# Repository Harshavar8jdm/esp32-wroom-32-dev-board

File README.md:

# ESP32-WROOM-32 Custom Development Board
**Designed by HTronics (Harsha Ganesh)**

A custom, breadboard-friendly development board for the ESP32-WROOM-32 module. This board features a modern USB-C interface, reliable serial communication via the CH340C, and an automatic bootloader entry circuit for seamless flashing.

</div>

---

## 📸 Project Showcase

### 3D Renders

### PCB Layout & Schematic

---

## ✨ Key Features

* **Modern Connectivity:** USB 2.0 Type-C receptacle with 5.1kΩ pull-down resistors on the CC lines, ensuring compatibility with standard Type-A to Type-C and Type-C to Type-C cables.
* **Auto-Programming Circuit:** Built-in two-transistor (SS8050) auto-reset circuit driven by DTR/RTS lines. No need to hold the "BOOT" button to flash firmware.
* **Robust Power Delivery:** Uses the AMS1117-3.3 LDO to step down 5V VBUS to a stable 3.3V for the ESP32, paired with 100nF and 10uF decoupling capacitors. Includes a B5819W Schottky diode for back-power protection.
* **USB-to-UART:** CH340C bridge provides reliable serial communication without requiring an external crystal oscillator.
* **User I/O:** Includes standard EN (Reset) and IO0 (Boot) tactile switches, a dedicated Red power LED, and a Green user LED mapped to GPIO 2.
* **Breadboard Friendly:** 2x15 pin headers break out all essential ESP32 GPIOs, strapping pins, and power rails.

---

## 🛠️ Hardware Overview & Schematic Sections

### 1. Power Supply (`AMS1117-3.3`)
The board takes 5V input from the USB-C VBUS line. A B5819W reverse-polarity protection diode prevents current from feeding back into the host device. The AMS1117-3.3 low-dropout regulator supplies up to 1A of 3.3V power, more than sufficient for the ESP32's RF transmission peaks. 

### 2. USB-to-UART Bridge (`CH340C`)
The CH340C handles USB data enumeration. 
* **Driver Note:** If you are using Linux (e.g., Fedora, Ubuntu), the CH340 driver is already built directly into the kernel—making it truly plug-and-play without any manual DNF/APT installations. Windows and macOS users may need to install the official WCH drivers.

### 3. Auto-Reset Circuit (`SS8050 Transistors`)
The CH340C toggles the `DTR` and `RTS` pins during the firmware upload sequence. The two SS8050 NPN transistors translate these signals into the precise timing sequence required to pull `EN` (Reset) low while `IO0` is held low, putting the ESP32 into flash mode automatically.

---

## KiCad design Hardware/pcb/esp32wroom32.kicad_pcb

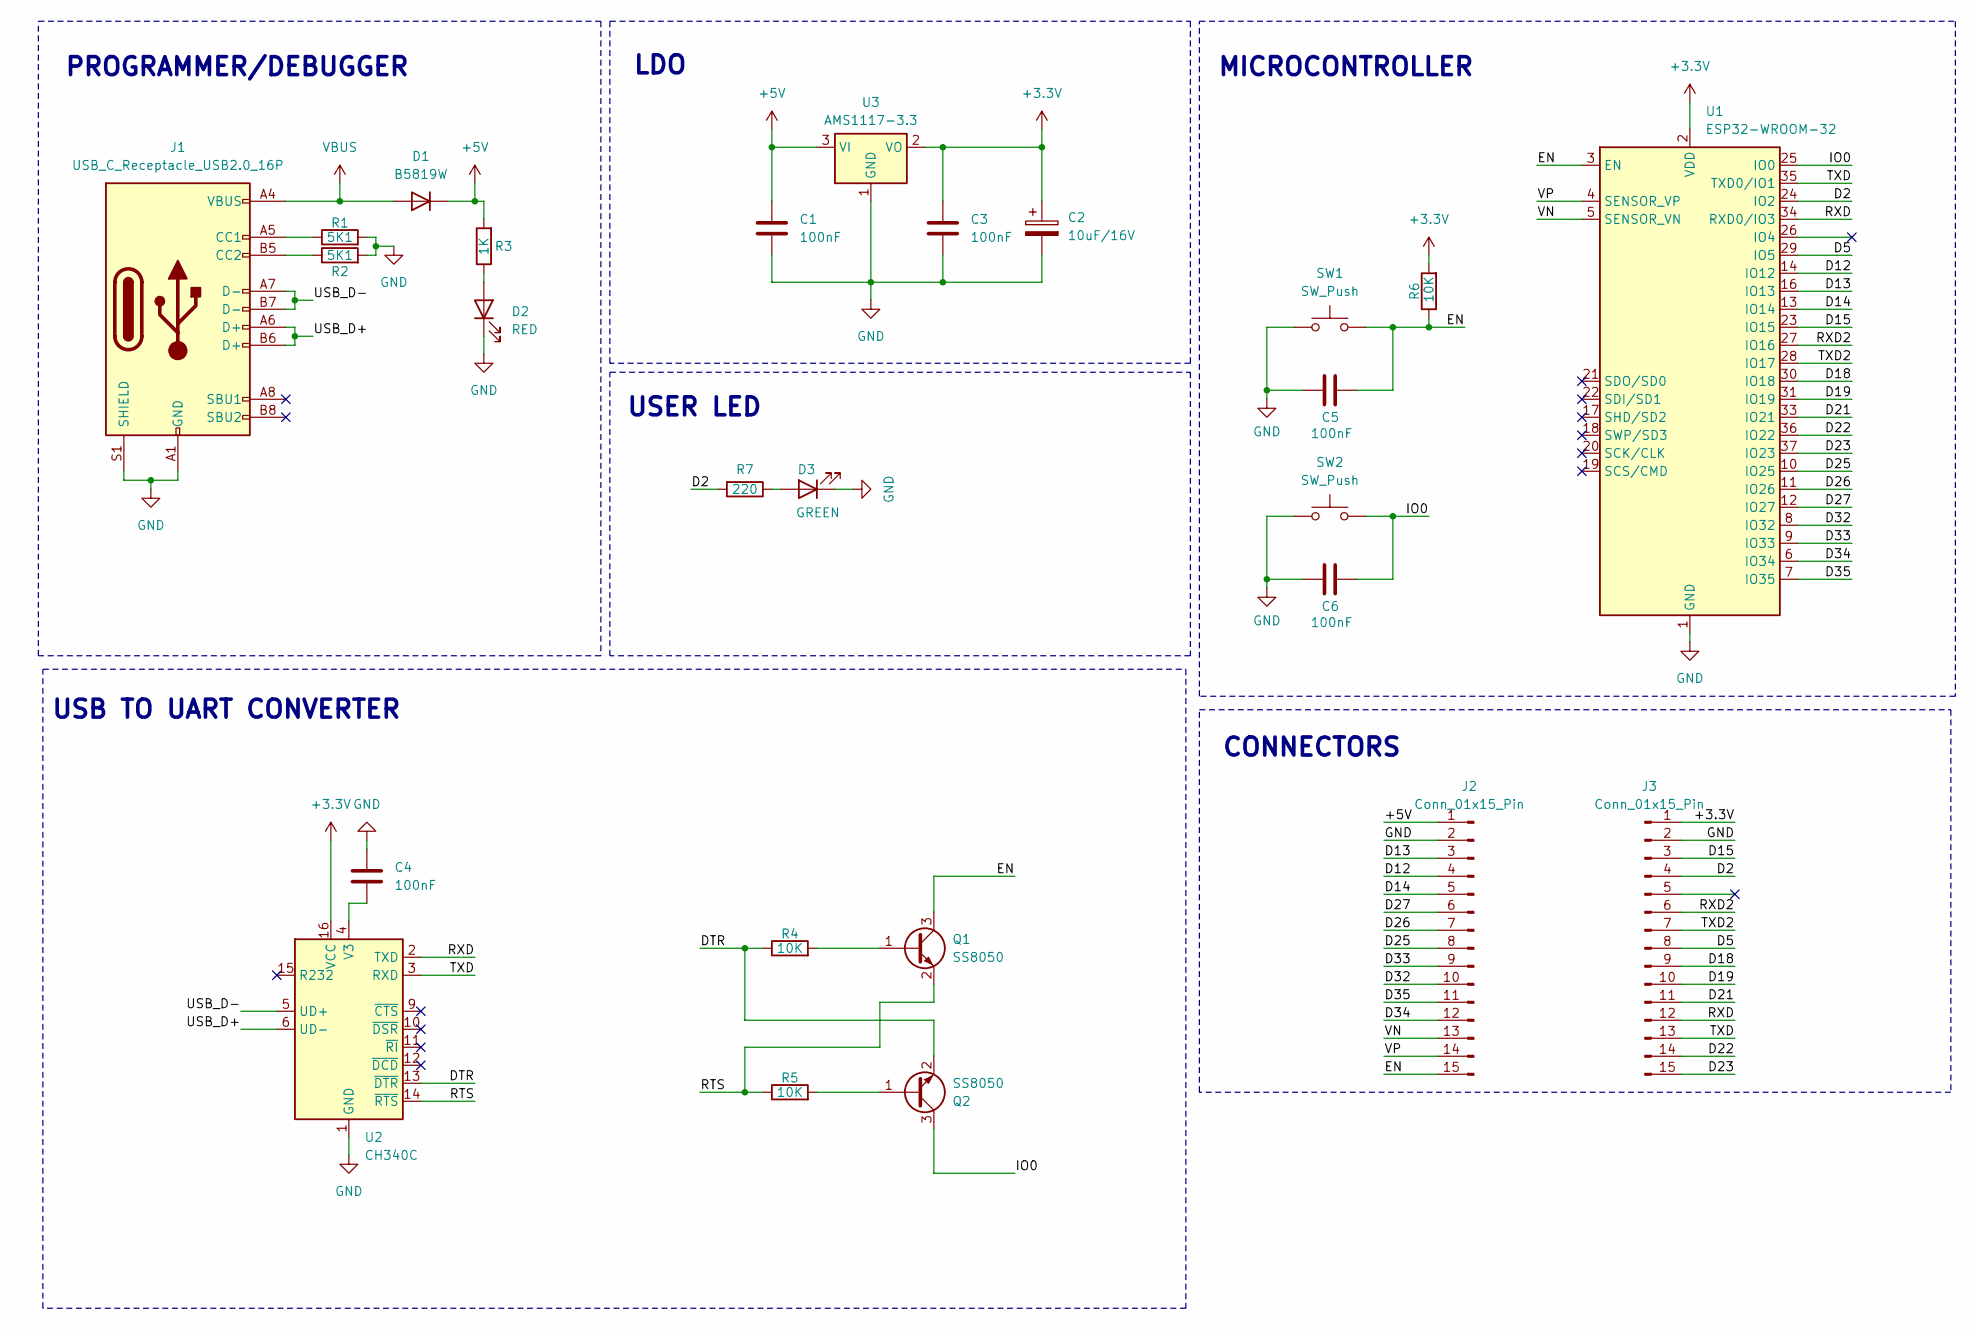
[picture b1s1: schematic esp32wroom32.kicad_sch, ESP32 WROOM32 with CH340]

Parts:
C1, C3, C4, C5, C6: 100nF; C_0603_1608Metric
C2: 10uF/16V; CP_EIA-3216-10_Kemet-I
D1: B5819W; D_0603_1608Metric
D2: RED; LED_0603_1608Metric
D3: GREEN; LED_0603_1608Metric
J1: USB_C_Receptacle_USB2.0_16P; USB_C_Receptacle_HRO_TYPE-C-31-M-12
J2, J3: Conn_01x15_Pin; PinHeader_1x15_P2.54mm_Vertical
Q1, Q2: SS8050; SOT-23
R1, R2: 5K1; R_0603_1608Metric
R3: 1K; R_0603_1608Metric
R4, R5, R6: 10K; R_0603_1608Metric
R7: 220; R_0603_1608Metric
SW1, SW2: SW_Push; SW_Push_SPST_NO_Alps_SKRK
U1: ESP32-WROOM-32
U2: CH340C; SOIC-16_3.9x9.9mm_P1.27mm
U3: AMS1117-3.3; SOT-223-3_TabPin2

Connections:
+3.3V: C2.1, C3.1, J3.1, R6.2, U1.2 (VDD), U2.16 (VCC), U3.2 (VO)
+5V: C1.1, D1.1 (K), J2.1, R3.2, U3.3 (VI)
/D2: J3.4, R7.2, U1.24 (IO2)
/D5: J3.8, U1.29 (IO5)
/D12: J2.4, U1.14 (IO12)
/D13: J2.3, U1.16 (IO13)
/D14: J2.5, U1.13 (IO14)
/D15: J3.3, U1.23 (IO15)
/D18: J3.9, U1.30 (IO18)
/D19: J3.10, U1.31 (IO19)
/D21: J3.11, U1.33 (IO21)
/D22: J3.14, U1.36 (IO22)
/D23: J3.15, U1.37 (IO23)
/D25: J2.8, U1.10 (IO25)
/D26: J2.7, U1.11 (IO26)
/D27: J2.6, U1.12 (IO27)
/D32: J2.10, U1.8 (IO32)
/D33: J2.9, U1.9 (IO33)
/D34: J2.12, U1.6 (IO34)
/D35: J2.11, U1.7 (IO35)
/DTR: Q2.2 (E), R4.1, U2.13 (~DTR)
/EN: C5.1, J2.15, Q1.3 (C), R6.1, SW1.2, U1.3 (EN)
/IO0: C6.1, Q2.3 (C), SW2.2, U1.25 (IO0)
/RTS: Q1.2 (E), R5.1, U2.14 (~RTS)
/RXD: J3.12, U1.34 (RXD0/IO3), U2.2 (TXD)
/RXD2: J3.6, U1.27 (IO16)
/TXD: J3.13, U1.35 (TXD0/IO1), U2.3 (RXD)
/TXD2: J3.7, U1.28 (IO17)
/USB_D+: J1.A6 (D+), J1.B6 (D+), U2.6 (UD-)
/USB_D-: J1.A7 (D-), J1.B7 (D-), U2.5 (UD+)
/VN: J2.13, U1.5 (SENSOR_VN)
/VP: J2.14, U1.4 (SENSOR_VP)
GND: C1.2, C2.2, C3.2, C4.1, C5.2, C6.2, D2.1 (K), D3.1 (K), J1.A1 (GND), J1.A12 (GND), J1.B1 (GND), J1.B12 (GND), J1.S1 (SHIELD), J2.2, J3.2, R1.2, R2.2, SW1.1, SW2.1, U1.1 (GND), U1.15 (GND), U1.38 (GND), U1.39 (GND), U2.1 (GND), U3.1 (GND)
unnamed: D2.2 (A), R3.1
unnamed: D3.2 (A), R7.1
unnamed: J1.A5 (CC1), R1.1
unnamed: J1.B5 (CC2), R2.1
unnamed: Q1.1 (B), R4.2
unnamed: Q2.1 (B), R5.2
unnamed: C4.2, U2.4 (V3)
VBUS: D1.2 (A), J1.A4 (VBUS), J1.A9 (VBUS), J1.B4 (VBUS), J1.B9 (VBUS)

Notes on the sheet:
USER LED
CONNECTORS
PROGRAMMER/DEBUGGER
LDO
USB TO UART CONVERTER
MICROCONTROLLER

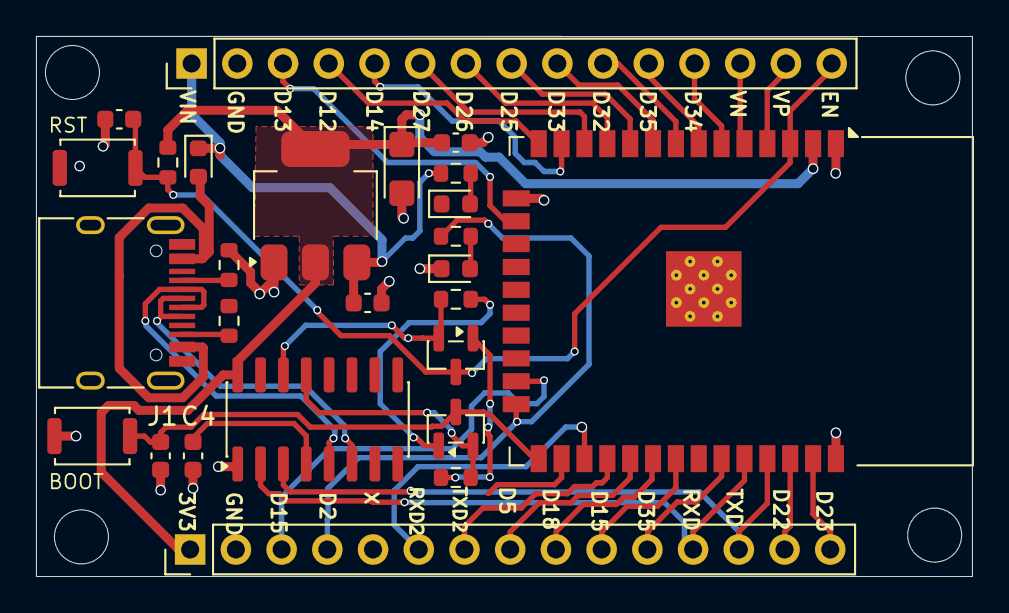
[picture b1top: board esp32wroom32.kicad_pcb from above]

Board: 2 copper layers, 52.0 x 30.0 mm, 26 parts (0 on the bottom side), 41 nets.
